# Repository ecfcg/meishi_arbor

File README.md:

# meishi_arbor

Original meishi keyboard.

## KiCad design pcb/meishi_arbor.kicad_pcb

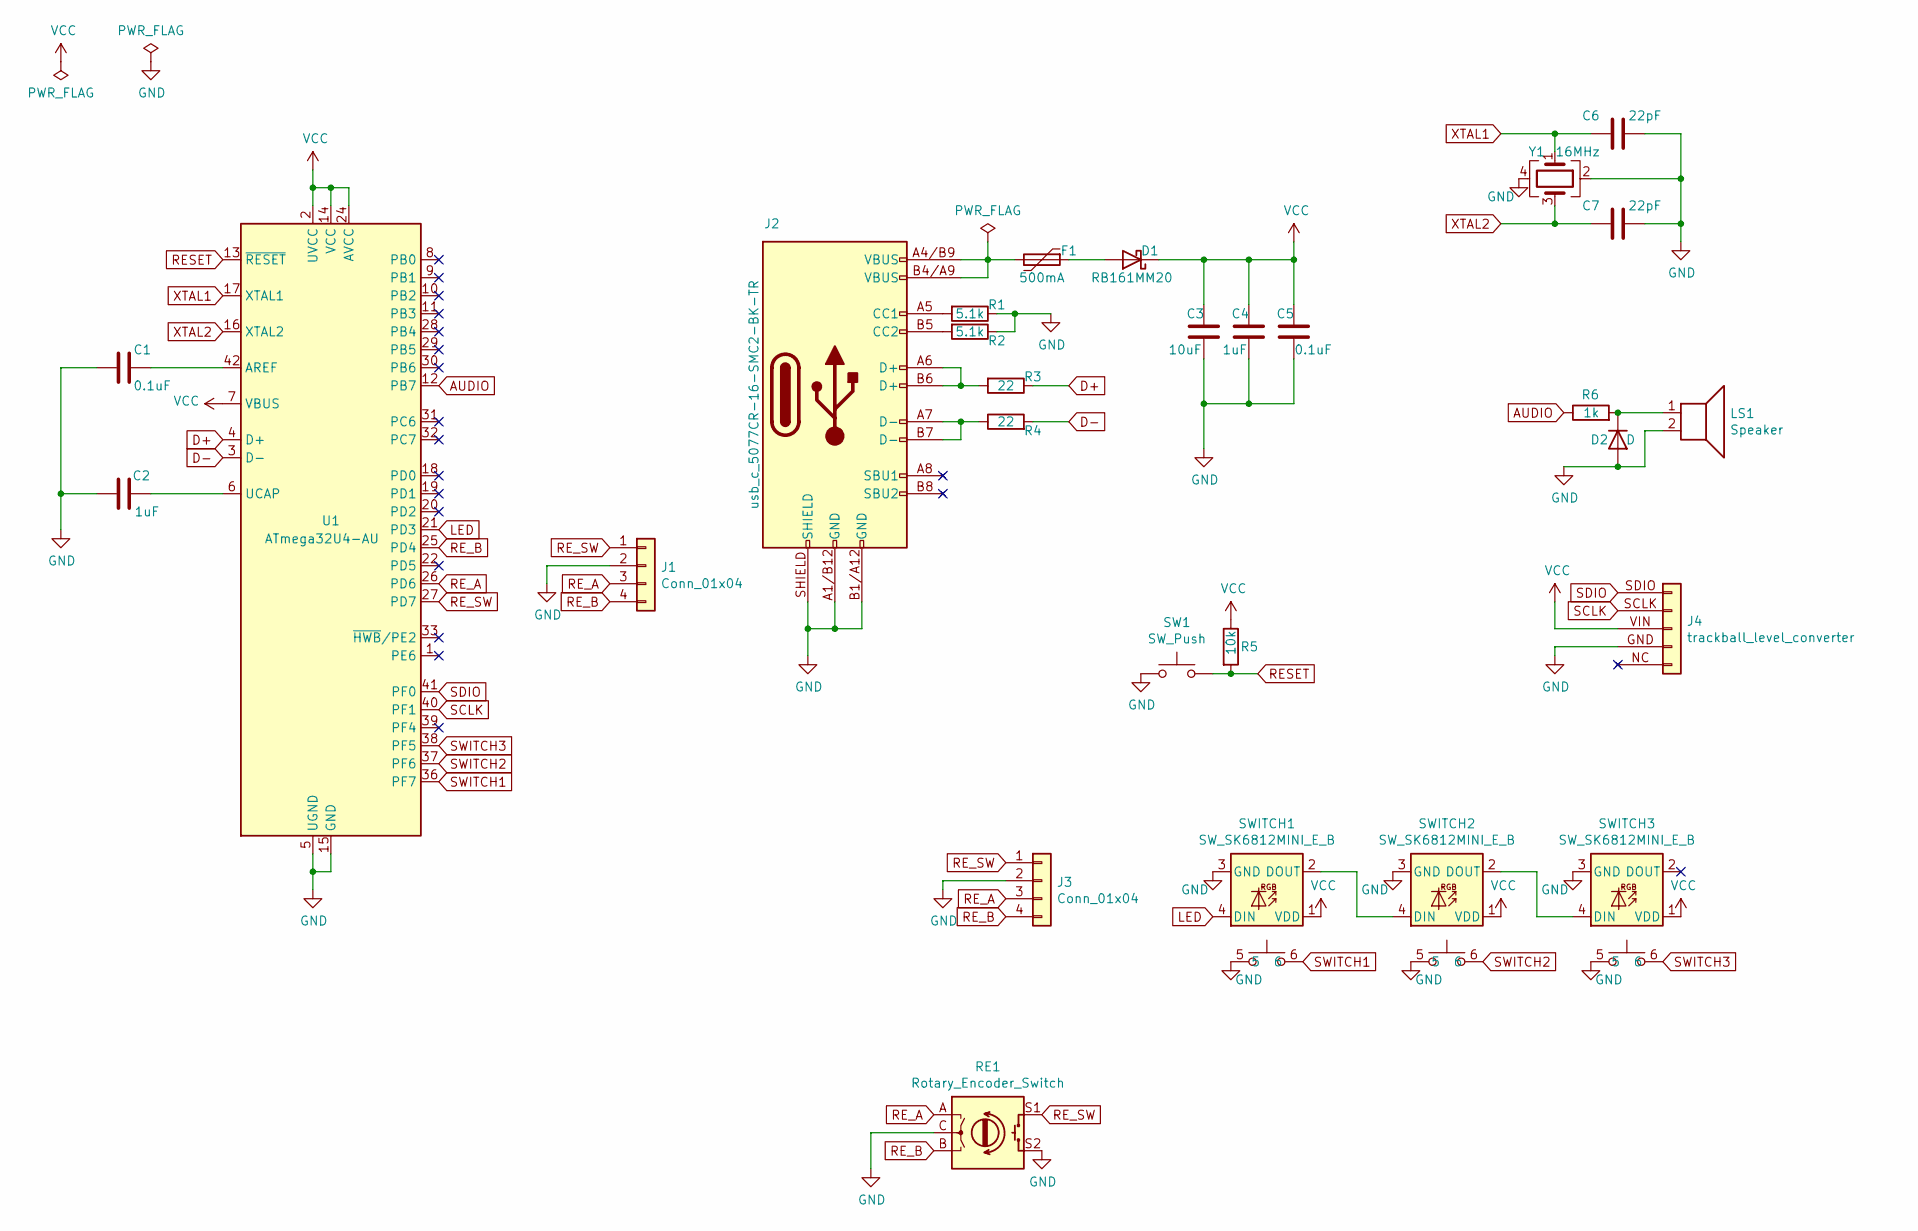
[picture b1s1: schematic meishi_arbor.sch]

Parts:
C1, C5: 0.1uF; smd_1206_3216mm
C2, C4: 1uF; smd_1206_3216mm
C3: 10uF; smd_1206_3216mm
C6, C7: 22pF; smd_1206_3216mm
D1: RB161MM20; schottky_barrier_diode_rb161mm20
D2: D; diode_1n4148_smd
F1: 500mA; fuse_littelfuse_2920L050DR
J1, J3: Conn_01x04; meishi_encoder
J2: usb_c_5077CR-16-SMC2-BK-TR; usb_c_5077CR-16SMC2-BK-TR
J4: trackball_level_converter
LS1: Speaker; Speaker_PKLCS1212E4001-R1
R1, R2: 5.1k; smd_1206_3216mm
R3, R4: 22; smd_1206_3216mm
R5: 10k; smd_1206_3216mm
R6: 1k; smd_1206_3216mm
RE1: Rotary_Encoder_Switch; Rotary_encoder_EC12
SW1: SW_Push; tact_sw_TVBP06-BN043CB-B
SWITCH1, SWITCH2, SWITCH3: SW_SK6812MINI_E_B; switch_w_sk6812mini-e_B
U1: ATmega32U4-AU; TQFP-44_10x10mm_P0.8mm
Y1: 16MHz; cryctal_epson_fa238

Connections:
AUDIO: R6.1, U1.12 (PB7)
D+: R3.1, U1.4 (D+)
D-: R4.2, U1.3 (D-)
GND: C1.2, C2.1, C3.2, C4.2, C5.2, C6.1, C7.1, D2.2 (A), J1.2, J2.A1/B12 (GND), J2.B1/A12 (GND), J2.SHIELD, J3.2, J4.GND, LS1.2, R1.1, R2.1, RE1.C, RE1.S2, SW1.1, SWITCH1.3 (GND), SWITCH1.5, SWITCH2.3 (GND), SWITCH2.5, SWITCH3.3 (GND), SWITCH3.5, U1.5 (UGND), U1.15 (GND), U1.23 (GND), U1.35 (GND), U1.43 (GND), Y1.2, Y1.4
LED: SWITCH1.4 (DIN), U1.21 (PD3)
unnamed: C1.1, U1.42 (AREF)
unnamed: C2.2, U1.6 (UCAP)
unnamed: D1.2 (A), F1.1
unnamed: D2.1 (K), LS1.1, R6.2
unnamed: F1.2, J2.A4/B9 (VBUS), J2.B4/A9 (VBUS)
unnamed: J2.A5 (CC1), R1.2
unnamed: J2.A6 (D+), J2.B6 (D+), R3.2
unnamed: J2.A7 (D-), J2.B7 (D-), R4.1
unnamed: J2.B5 (CC2), R2.2
unnamed: SWITCH1.2 (DOUT), SWITCH2.4 (DIN)
unnamed: SWITCH2.2 (DOUT), SWITCH3.4 (DIN)
RESET: R5.2, SW1.2, U1.13 (~RESET)
RE_A: J1.3, J3.3, RE1.A, U1.26 (PD6)
RE_B: J1.4, J3.4, RE1.B, U1.25 (PD4)
RE_SW: J1.1, J3.1, RE1.S1, U1.27 (PD7)
SCLK: J4.SCLK, U1.40 (PF1)
SDIO: J4.SDIO, U1.41 (PF0)
SWITCH1: SWITCH1.6, U1.36 (PF7)
SWITCH2: SWITCH2.6, U1.37 (PF6)
SWITCH3: SWITCH3.6, U1.38 (PF5)
VCC: C3.1, C4.1, C5.1, D1.1 (K), J4.VIN, R5.1, SWITCH1.1 (VDD), SWITCH2.1 (VDD), SWITCH3.1 (VDD), U1.2 (UVCC), U1.7 (VBUS), U1.14 (VCC), U1.24 (AVCC), U1.34 (VCC), U1.44 (AVCC)
XTAL1: C6.2, U1.17 (XTAL1), Y1.1
XTAL2: C7.2, U1.16 (XTAL2), Y1.3

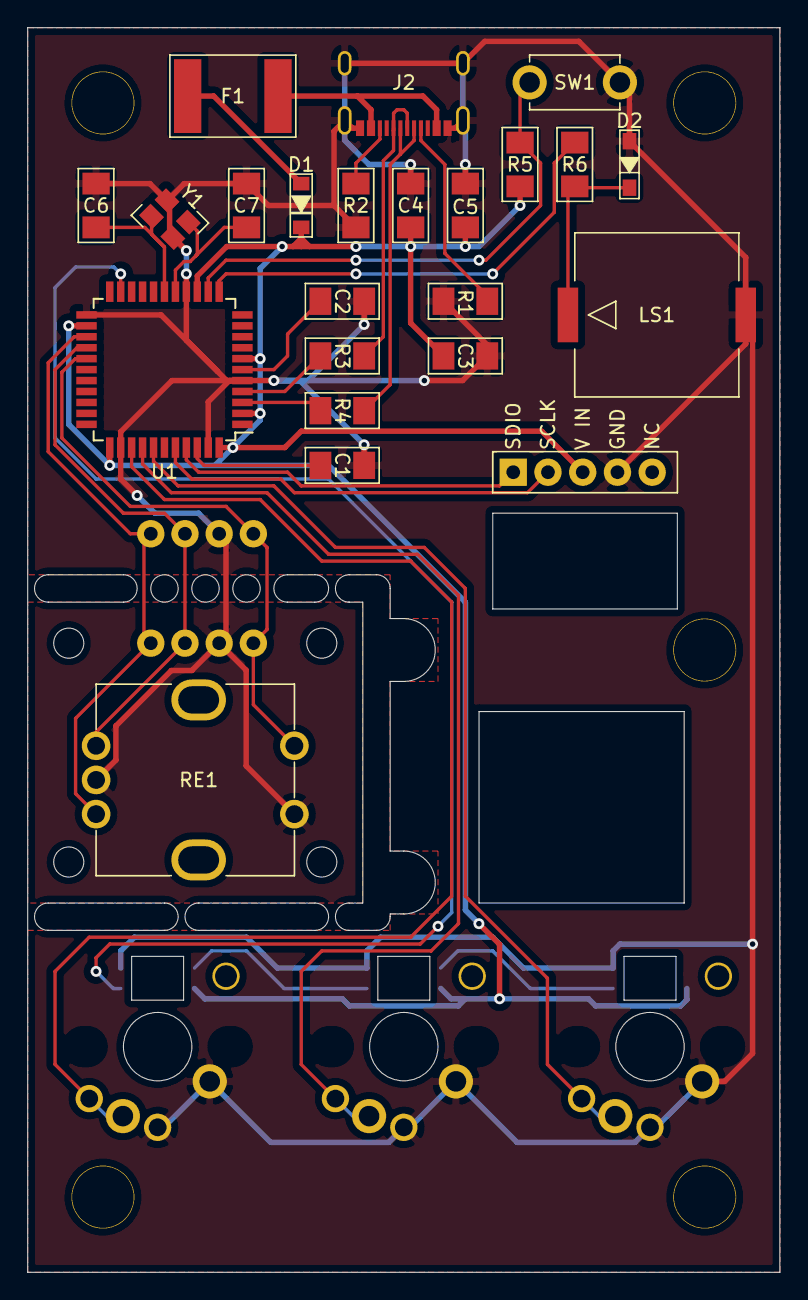
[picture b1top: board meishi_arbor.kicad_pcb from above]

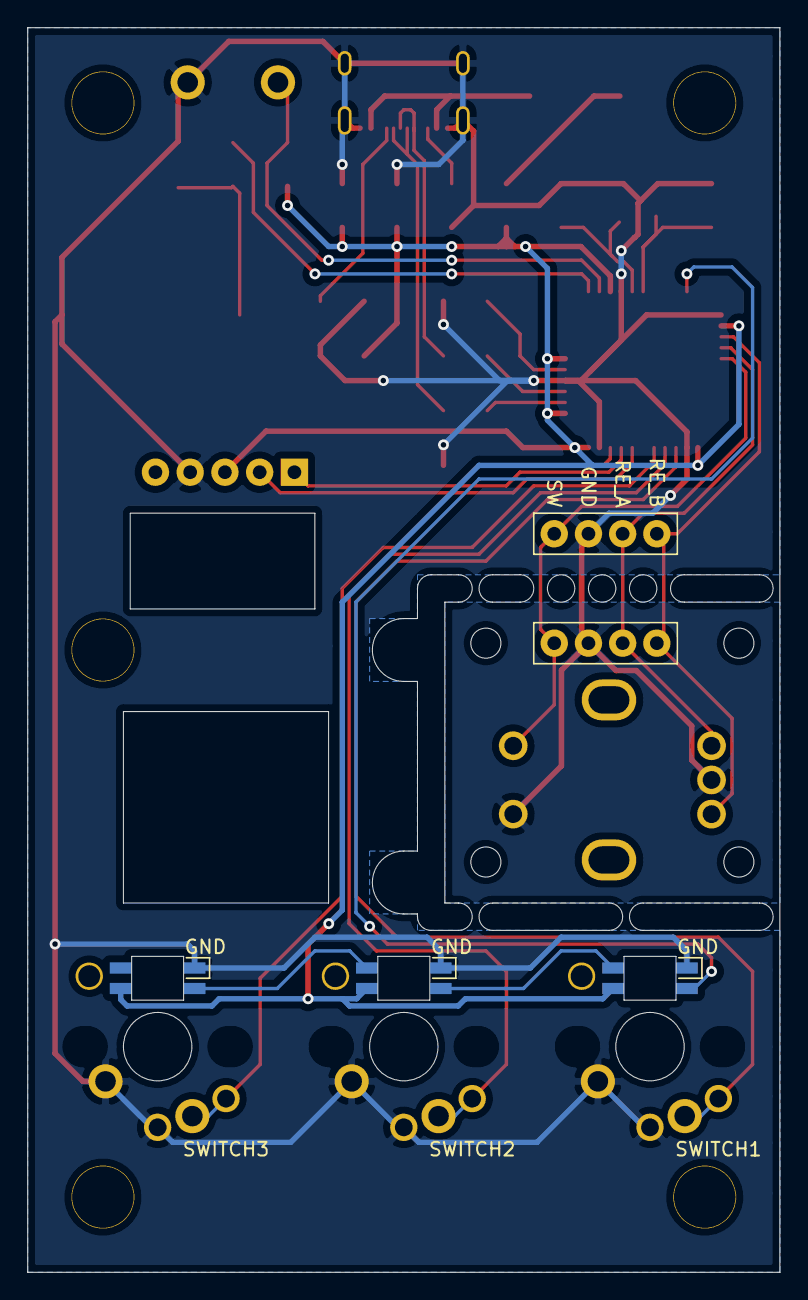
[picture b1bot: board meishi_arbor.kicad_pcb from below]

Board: 2 copper layers, 55.0 x 91.0 mm, 28 parts (5 on the bottom side), 28 nets.

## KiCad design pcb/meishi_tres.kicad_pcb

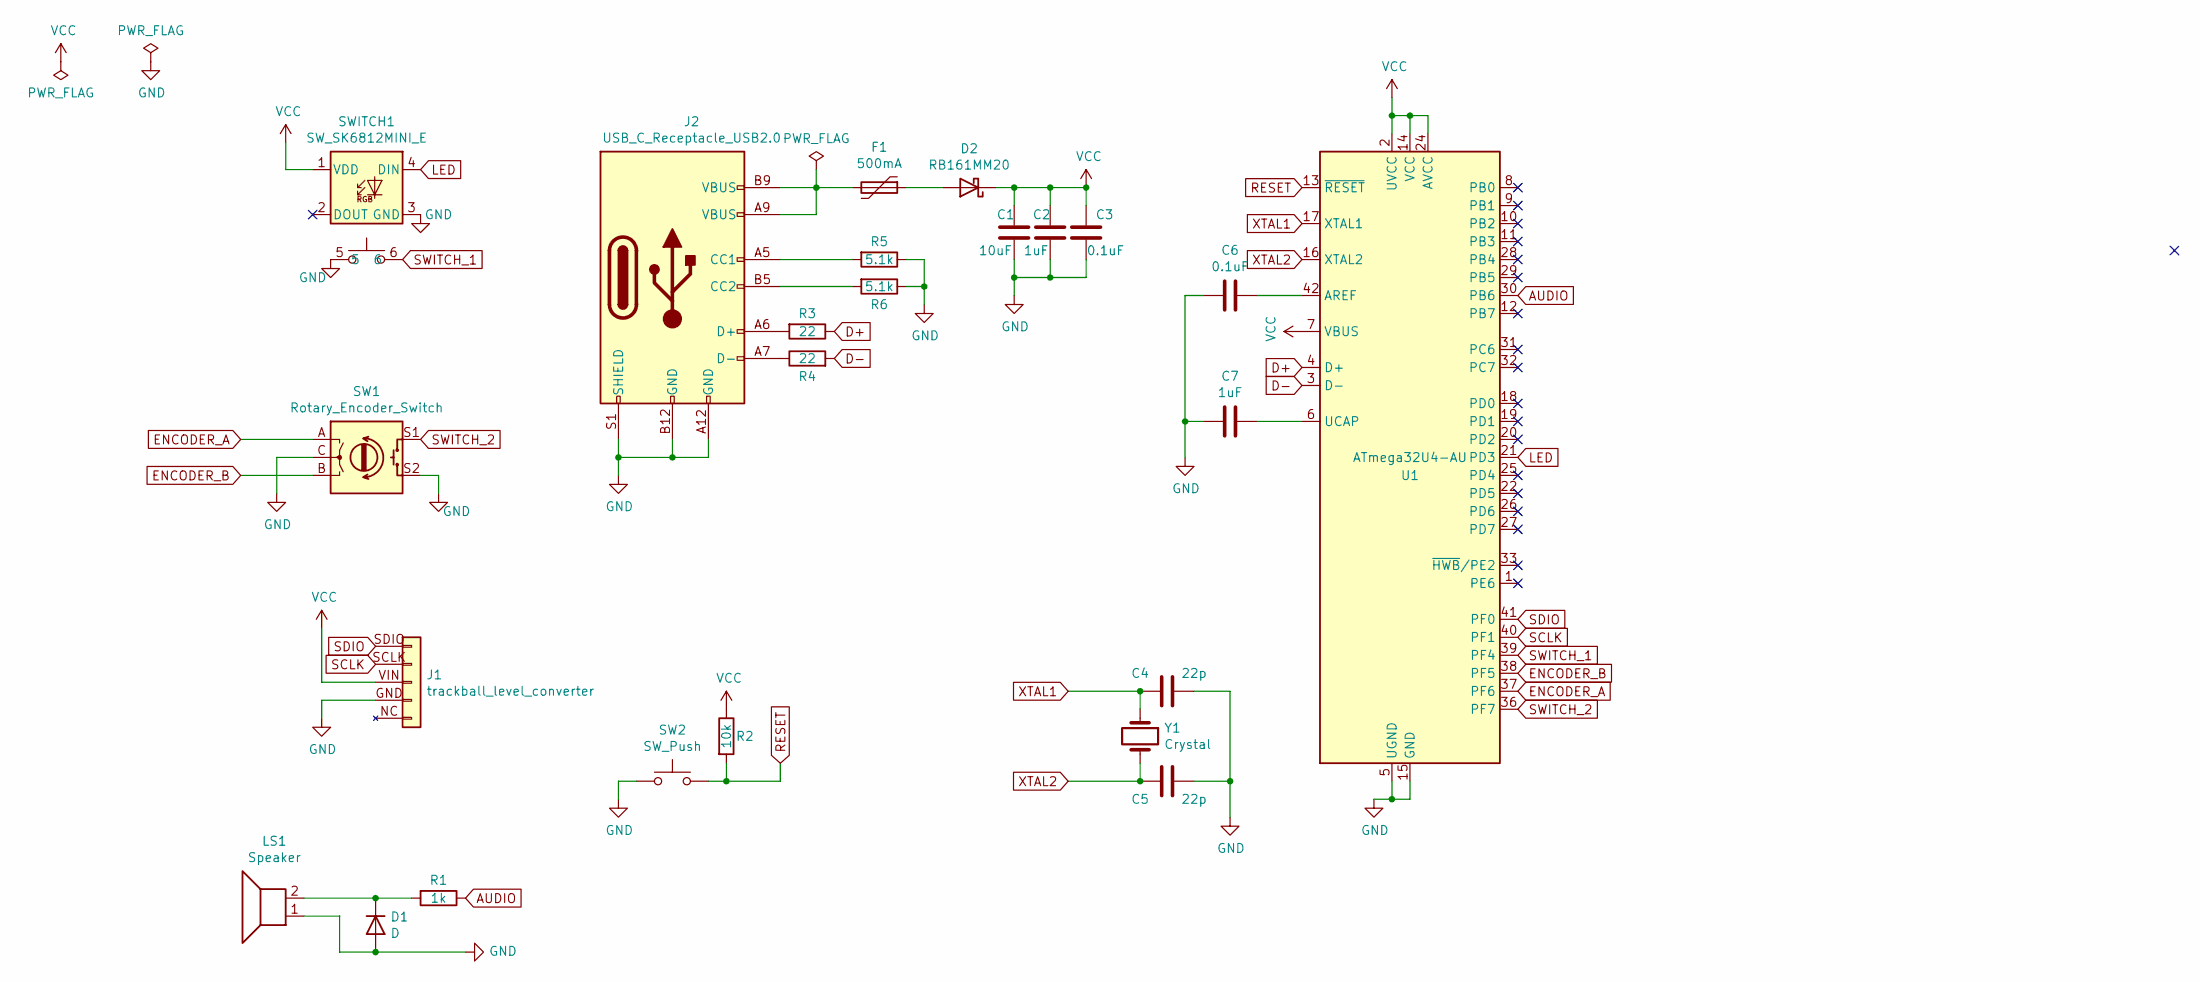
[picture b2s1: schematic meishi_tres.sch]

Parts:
C1: 10uF; capacitor_th_5.0mm
C2, C7: 1uF; capacitor_th_5.0mm
C3, C6: 0.1uF; capacitor_th_5.0mm
C4, C5: 22p; capacitor_th_2.5mm
D1: D; D_1N4148W_SMD_SH
D2: RB161MM20; schottky_barrier_diode
F1: 500mA; resettable_fuse_RXEF050
J1: trackball_level_converter; trackball_level_converter_rev
J2: USB_C_Receptacle_USB2.0; U2CF8PA_usb_type_c_receptacle
LS1: Speaker; Speaker_PKLCS1212E4001-R1
R1: 1k; resister_th_7.5mm
R2: 10k; resister_th_7.5mm
R3, R4: 22; resister_th_7.5mm
R5, R6: 5.1k; resister_th_5.0mm
SW1: Rotary_Encoder_Switch; Rotary_encoder_EC12
SW2: SW_Push; tact_sw_TVBP06-BN043CB-B
SWITCH1: SW_SK6812MINI_E; kailh_choc_socket_w_sk6812mini-e_A
U1: ATmega32U4-AU; TQFP-44_10x10mm_P0.8mm
Y1: Crystal; Crystal_16Mhz_2pin

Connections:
AUDIO: R1.1, U1.30 (PB6)
D+: R3.1, U1.4 (D+)
D-: R4.2, U1.3 (D-)
ENCODER_A: SW1.A, U1.37 (PF6)
ENCODER_B: SW1.B, U1.38 (PF5)
GND: C1.2, C2.2, C3.2, C4.1, C5.1, C6.1, C7.2, D1.2 (A), J1.GND, J2.A12 (GND), J2.B12 (GND), J2.S1 (SHIELD), LS1.1, R5.1, R6.1, SW1.C, SW1.S2, SW2.1, SWITCH1.3 (GND), SWITCH1.5, U1.5 (UGND), U1.15 (GND), U1.23 (GND), U1.35 (GND), U1.43 (GND)
LED: SWITCH1.4 (DIN), U1.21 (PD3)
unnamed: C6.2, U1.42 (AREF)
unnamed: C7.1, U1.6 (UCAP)
unnamed: D1.1 (K), LS1.2, R1.2
unnamed: D2.2 (A), F1.1
unnamed: F1.2, J2.A9 (VBUS), J2.B9 (VBUS)
unnamed: J2.A5 (CC1), R5.2
unnamed: J2.A6 (D+), R3.2
unnamed: J2.A7 (D-), R4.1
unnamed: J2.B5 (CC2), R6.2
RESET: R2.2, SW2.2, U1.13 (~RESET)
SCLK: J1.SCLK, U1.40 (PF1)
SDIO: J1.SDIO, U1.41 (PF0)
SWITCH_1: SWITCH1.6, U1.39 (PF4)
SWITCH_2: SW1.S1, U1.36 (PF7)
VCC: C1.1, C2.1, C3.1, D2.1 (K), J1.VIN, R2.1, SWITCH1.1 (VDD), U1.2 (UVCC), U1.7 (VBUS), U1.14 (VCC), U1.24 (AVCC), U1.34 (VCC), U1.44 (AVCC)
XTAL1: C4.2, U1.17 (XTAL1), Y1.1
XTAL2: C5.2, U1.16 (XTAL2), Y1.2

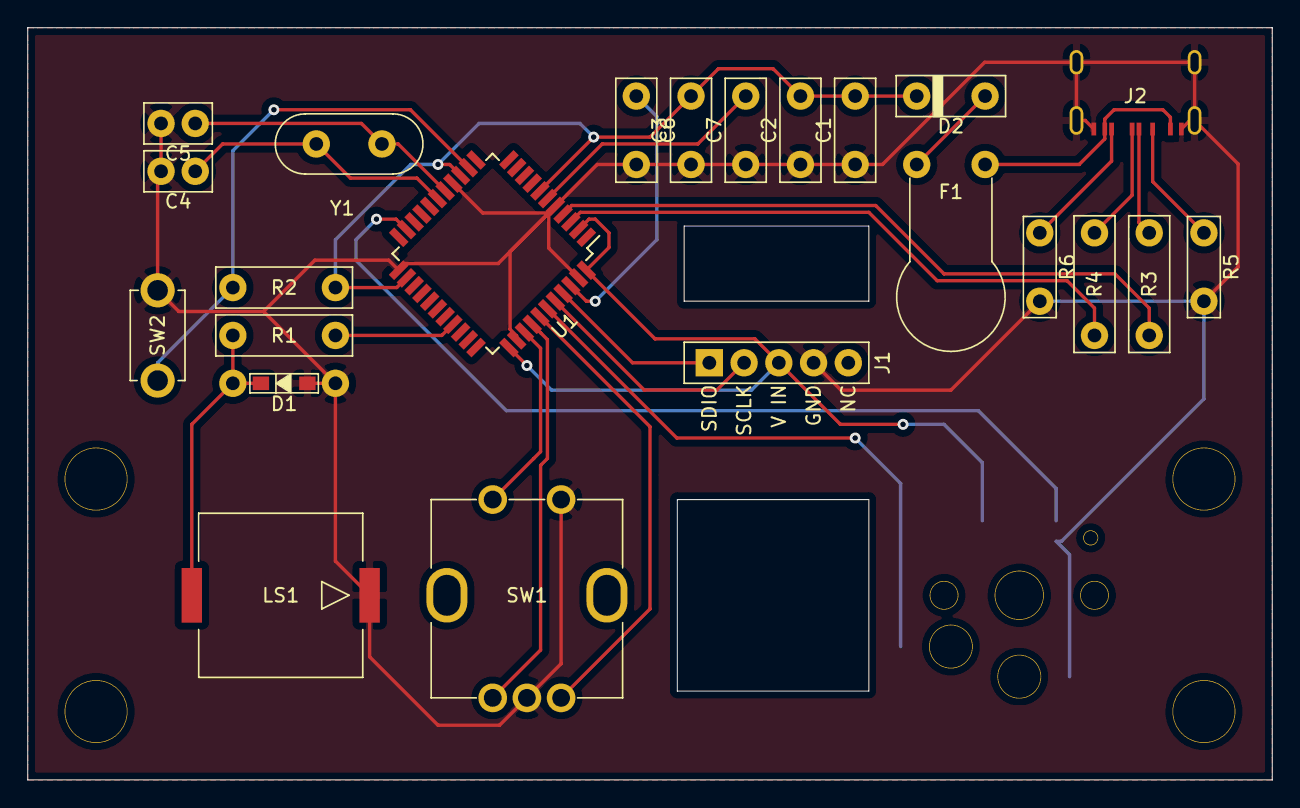
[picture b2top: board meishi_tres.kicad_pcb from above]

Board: 2 copper layers, 91.0 x 55.0 mm, 24 parts (1 on the bottom side), 24 nets.

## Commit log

2020-06-12 Typo correction
2020-06-24 Add .gitignore
2020-06-24 ドラフト版を作成
2020-07-19 プロジェクト名称を変更
2020-08-02 表面実装に変更
2020-08-02 構造用プレートを追加
2020-08-02 gerber出力後のファイルを保存
2020-08-02 gerberを無視する
2020-08-03 gerber出力
2020-08-10 kicadライブラリをsubmodule化
2020-08-10 ライブラリを相対パスに変更
2020-08-11 アクリルカバーを作成
2020-08-11 配置を微修正
